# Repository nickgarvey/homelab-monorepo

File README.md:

# Nick's Homelab

Everything that runs the homelab, in one repo with one Nix flake:

* `hosts/`: NixOS configurations for each machine
* `modules/`: Reusable NixOS modules (e.g. `core/nixos-common` is applied to all hosts)
* `patches/`: Patches applied to upstream packages, and the ones worth upstreaming
* `secrets/`: SOPS-encrypted secrets for the hosts
* `docs/`: Notes and troubleshooting docs
* `devshells/`: Nix dev shells
* `packages/`: Software built here — packages, container images, and the `deploy` tool
* `k8s/`: Kubernetes manifests for the k3s cluster
* `firmware/`: ESP32 device firmware

Conventions for working in the repo are in [`AGENTS.md`](AGENTS.md).

## Hardware

| Host | Machine | CPU | RAM | GPU | Primary storage |
|------|---------|-----|-----|-----|-----------------|
| [`talos`](hosts/talos) | MSI PRO X870E-P WIFI | AMD Ryzen 9 9950X3D | 64 GB | NVIDIA RTX 5090 | Kingston SNV2S 500 GB NVMe + Crucial T705 4 TB NVMe |
| [`lydia`](hosts/lydia) | ASRock Industrial IMB-X1314 | Intel i5-12600K | 128 GB | iGPU (UHD 770) | Samsung 980 Pro 2 TB NVMe + 2× WDC 6 TB HDD |
| [`fus`](hosts/fus) | Beelink EQ14 Mini PC | Intel N150 | 16 GB | iGPU (Alder Lake-N) | Crucial P3 500 GB NVMe |
| [`ro`](hosts/ro) | Beelink EQ14 Mini PC | Intel N150 | 16 GB | iGPU (Alder Lake-N) | Crucial P3 500 GB NVMe |
| [`dah`](hosts/dah) | Beelink EQ14 Mini PC | Intel N150 | 16 GB | iGPU (Alder Lake-N) | Crucial P3 500 GB NVMe |
| [`joor`](hosts/joor) | Beelink EQi Mini PC | Intel Core 3 304 (Wildcat Lake) | 32 GB | iGPU (Xe, Wildcat Lake) | YMTC 512 GB UFS + WD Blue SN5100 4 TB NVMe |
| [`zah`](hosts/zah) | Beelink EQi Mini PC | Intel Core 3 304 (Wildcat Lake) | 32 GB | iGPU (Xe, Wildcat Lake) | YMTC 512 GB UFS + WD Blue SN5100 4 TB NVMe |
| [`frul`](hosts/frul) | Beelink EQi Mini PC | Intel Core 3 304 (Wildcat Lake) | 32 GB | iGPU (Xe, Wildcat Lake) | YMTC 512 GB UFS + WD Blue SN5100 4 TB NVMe |
| [`wabbajack`](hosts/wabbajack) | Framework Desktop | AMD Ryzen AI Max+ 395 (Strix Halo) | 128 GB | Radeon 8060S iGPU | WD_BLACK SN850X 2 TB NVMe + WD_BLACK SN7100 2 TB NVMe |
| [`dovahkiin`](hosts/dovahkiin) | Framework Laptop 13 | AMD Ryzen AI 7 350 | 64 GB | Radeon 860M iGPU | KIOXIA 2 TB NVMe |
| [`dragonsreach`](hosts/dragonsreach) | Topton Fanless PC| Intel N150 | 16 GB | iGPU (Alder Lake-N) | Samsung 870 QVO 1 TB SATA |
| [`skyforge`](hosts/skyforge) | Raspberry Pi 5 | Broadcom BCM2712 | — | VideoCore VII | microSD |

### Kubernetes Hosts

`fus`, `ro` and `dah` are the control-plane nodes of the Kubernetes cluster.
`joor`, `zah` and `frul` join as workers (`services.k3s.role = "agent"`) and also
run the Ceph storage cluster on their 4 TB drives.

[`modules/k3s/k3s-common.nix`](modules/k3s/k3s-common.nix) contain the main configuration for those hosts.

Services running on that cluster are found in [`k8s/`](k8s/).

### Servers

`lydia` has 128GB of DDR4 ECC RAM, so it acts as a storage/VM server.

`wabbajack` is the 128GB model of the Framework Desktop.

### Workstations
`talos` is the big desktop: 9950X3D and an RTX 5090, on a 500GB OS drive plus a 4TB btrfs carrying `/nix`, `/home` and `/var`.

`dovahkiin` is a AMD Ryzen AI 7 350 mainboard laptop with 64GB RAM I got off eBay. Eager to upgrade to a Panther Lake mainboard but going to wait for RAM to come down.

### Router
TopTon fanless PC with an Intel N150. 4x 2.5G NICs but I only use two of them (WAN/LAN).

## Installing a new host

Machines PXE-boot the live rescue/install environment off the LAN — `lydia`
serves it, no USB stick needed. See [`docs/netboot.md`](docs/netboot.md).

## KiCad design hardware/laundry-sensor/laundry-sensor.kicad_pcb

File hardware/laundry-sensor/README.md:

# laundry-sensor

Battery-powered vibration sensor for the washer: ESP32-C6 module, LIS2DW12
accelerometer, SHT40, 2×AA through a TPS63900 buck-boost, reporting over
Matter/Thread. Firmware lives in `firmware/devices/laundry-sensor/`.

Work in `nix develop .#pcb`.

- `circuit.py`: the circuit in SKiDL. `python3 circuit.py` runs ERC and writes `laundry-sensor.net`.
- `report.py`: prints the parts list and every net as Markdown, for review.
- `gen_footprints.py`: writes footprints KiCad's libraries lack (LIS2DW12) into `footprints/laundry.pretty`.
- `build_pcb.py`: writes `laundry-sensor.kicad_pcb` from the circuit: footprints, nets, placement, outline.
- `check.sh [dir]`: design-rule check summary plus top/bottom SVG renders.
- `route_pcb.py`: routes the board in place (run after `build_pcb.py`): net classes, the TPS63900
  loops by hand, a via from every SMD GND pad, Freerouting for the rest, then ground pours on both
  layers with stitching vias. Freerouting varies between runs, so it keeps the best of up to five.
- `fab.py`: writes JLCPCB files into `fab/`: `laundry-sensor-gerbers.zip`, `laundry-sensor-bom.csv`
  and `laundry-sensor-cpl.csv`. Its `CORRECTIONS` table turns KiCad rotations and origins into
  JLC's (EasyEDA's) for the packages that differ.

## Ordering from JLCPCB

1. Upload `fab/laundry-sensor-gerbers.zip`. 2 layers, 1.6 mm, 87×37 mm; defaults otherwise
   (lead-free HASL is fine; ENIG is flatter for the 0.5 mm-pitch LGA and WSON).
2. Turn on PCB Assembly, top side, Standard (JLC places the ESP32 module only with Standard).
   Edge rails added by JLC go on the long sides; snap them off after assembly. Upload the BOM and CPL.
3. In the placement preview, check pin 1 of U1 (TPS63900), U3 (LIS2DW12) and U4 (SHT40), and the
   outline of U2 (ESP32-C6 module). Their rotations and origins come from fitting the EasyEDA
   footprints to KiCad's, but JLC can keep its own per-part rotation.
4. BT1 (battery holder, back side) and J2 (PPK2 header) are through-hole and not in the BOM:
   solder them by hand. Fit a jumper on J2 unless a PPK2 is connected.

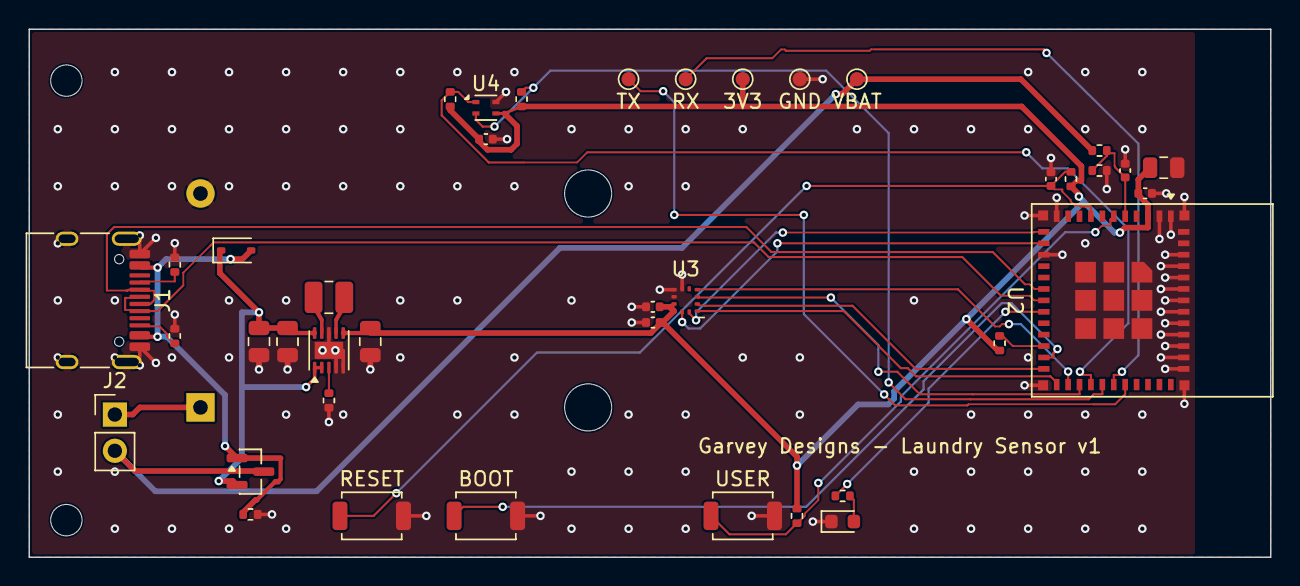
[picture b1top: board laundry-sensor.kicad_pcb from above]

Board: 2 copper layers, 87.0 x 37.0 mm, 43 parts (1 on the bottom side), 30 nets.

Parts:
BT1: 2xAA; BatteryHolder_Keystone_2462_2xAA
C1, C2, C3, C5: 22uF; C_0805_2012Metric
C4, C6, C7, C8, C9, C10: 100nF; C_0402_1005Metric
D1: 1N4148WS; D_SOD-323
D2: red; LED_0603_1608Metric
H1, H2: MountingHole_2.2mm_M2
J1: USB_C_Receptacle_USB2.0_16P; USB_C_Receptacle_HRO_TYPE-C-31-M-12
J2: PPK2; PinHeader_1x02_P2.54mm_Vertical
L1: 2.2uH; L_1008_2520Metric
Q1: AO3401A; SOT-23
R1, R5, R7: 100k; R_0402_1005Metric
R2: 36.5k; R_0402_1005Metric
R3, R4: 10M; R_0402_1005Metric
R6, R11, R12: 10k; R_0402_1005Metric
R8, R9, R10: 5.1k; R_0402_1005Metric
SW1: RESET; SW_SPST_TS-1088-xR020
SW2: BOOT; SW_SPST_TS-1088-xR020
SW3: USER; SW_SPST_TS-1088-xR020
TP1: TX; TestPoint_Pad_D1.0mm
TP2: RX; TestPoint_Pad_D1.0mm
TP3: 3V3; TestPoint_Pad_D1.0mm
TP4: GND; TestPoint_Pad_D1.0mm
TP5: VBAT; TestPoint_Pad_D1.0mm
U1: TPS63900; WSON-10-1EP_2.5x2.5mm_P0.5mm_EP1.2x2mm
U2: ESP32-C6-MINI-1
U3: LIS2DW12; LIS2DW12_LGA-12_2x2mm_P0.5mm
U4: SHT40-AD1B; Sensirion_DFN-4_1.5x1.5mm_P0.8mm_SHT4x_NoCentralPad

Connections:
+3V3: C3.1, C5.1, C6.1, C8.1, C9.1, C10.1, R5.1, R6.1, R7.1, R11.1, R12.1, TP3.1, U1.6, U2.3, U3.9, U3.10, U4.3
ACC_CS: U2.24, U3.2
ACC_INT1: U2.12, U3.12
ACC_INT2: U2.13, U3.11
ACC_MISO: U2.27, U3.3
ACC_MOSI: U2.26, U3.4
ACC_SCLK: U2.25, U3.1
BAT+: BT1.1, J2.1
BOOT: SW2.1, U2.23
EN: C7.1, R5.2, SW1.1, U2.8
GND: BT1.2, C1.2, C2.2, C3.2, C4.2, C5.2, C6.2, C7.2, C8.2, C9.2, C10.2, D2.1, J1.A1, J1.A12, J1.B1, J1.B12, J1.SH, R1.2, R2.2, R4.2, R9.2, R10.2, SW1.2, SW2.2, SW3.2, TP4.1, U1.4, U1.5, U1.8, U1.11, U2.1, U2.2, U2.11, U2.14, U2.36, U2.37, U2.38, U2.39, U2.40, U2.41, U2.42, U2.43, U2.44, U2.45, U2.46, U2.47, U2.48, U2.49, U2.50, U2.51, U2.52, U2.53, U3.6, U3.7, U3.8, U4.4
I2C_SCL: R12.2, U2.29, U4.2
I2C_SDA: R11.2, U2.28, U4.1
LED_A: D2.2, R8.2
unnamed: R2.1, U1.3
unnamed: L1.1, U1.9
unnamed: L1.2, U1.7
unnamed: R6.2, U2.22
unnamed: R8.1, U2.19
unnamed: J1.A5, R9.1
unnamed: J1.B5, R10.1
UART_RX: TP2.1, U2.30
UART_TX: TP1.1, U2.31
USB_D+: J1.A6, J1.B6, U2.18
USB_D-: J1.A7, J1.B7, U2.17
USER_BTN: R7.2, SW3.1, U2.6
VBAT: J2.2, Q1.3, R3.1, TP5.1
VBAT_SENSE: C4.1, R3.2, R4.1, U2.5
VBUS: D1.2, J1.A4, J1.A9, J1.B4, J1.B9, Q1.1, R1.1
VIN: C1.1, C2.1, D1.1, Q1.2, U1.1, U1.2, U1.10

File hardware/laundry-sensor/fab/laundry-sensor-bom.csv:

Comment,Designator,Footprint,LCSC Part #
22uF,"C1,C2,C3,C5",C_0805_2012Metric,C45783
100nF,"C4,C6,C7,C8,C9,C10",C_0402_1005Metric,C1525
1N4148WS,D1,D_SOD-323,C2128
red,D2,LED_0603_1608Metric,C2286
USB_C_Receptacle_USB2.0_16P,J1,USB_C_Receptacle_HRO_TYPE-C-31-M-12,C165948
2.2uH,L1,L_1008_2520Metric,C1017131
AO3401A,Q1,SOT-23,C15127
100k,"R1,R5,R7",R_0402_1005Metric,C25741
36.5k,R2,R_0402_1005Metric,C25887
10M,"R3,R4",R_0402_1005Metric,C144806
10k,"R6,R11,R12",R_0402_1005Metric,C25744
5.1k,"R8,R9,R10",R_0402_1005Metric,C25905
RESET,SW1,SW_SPST_TS-1088-xR020,C720477
BOOT,SW2,SW_SPST_TS-1088-xR020,C720477
USER,SW3,SW_SPST_TS-1088-xR020,C720477
TPS63900,U1,WSON-10-1EP_2.5x2.5mm_P0.5mm_EP1.2x2mm,C1518762
ESP32-C6-MINI-1,U2,ESP32-C6-MINI-1,C5736265
LIS2DW12,U3,LIS2DW12_LGA-12_2x2mm_P0.5mm,C189624
SHT40-AD1B,U4,Sensirion_DFN-4_1.5x1.5mm_P0.8mm_SHT4x_NoCentralPad,C2909890

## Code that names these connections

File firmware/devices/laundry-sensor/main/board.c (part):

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/* hardware/laundry-sensor/circuit.py */
#define PIN_LED        GPIO_NUM_14   /* through 5.1k to the LED, active high */
#define PIN_BUTTON     GPIO_NUM_3    /* USER, 100k pull-up on the board, active low */
#define PIN_ACC_INT1   GPIO_NUM_0
#define PIN_ACC_INT2   GPIO_NUM_1
#define PIN_ACC_CS     GPIO_NUM_18
#define PIN_ACC_SCLK   GPIO_NUM_19
#define PIN_ACC_MOSI   GPIO_NUM_20
#define PIN_ACC_MISO   GPIO_NUM_21
#define PIN_I2C_SDA    GPIO_NUM_22
#define PIN_I2C_SCL    GPIO_NUM_23
#define PIN_VBAT_SENSE GPIO_NUM_2
#else
/* Adafruit ESP32-C6 Feather */
#define PIN_LED        GPIO_NUM_15   /* red LED, active high */
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static bool accel_init(void)
{
    spi_bus_config_t bus = {
        .mosi_io_num = PIN_ACC_MOSI,
        .miso_io_num = PIN_ACC_MISO,
        .sclk_io_num = PIN_ACC_SCLK,
        .quadwp_io_num = -1,
        .quadhd_io_num = -1,
    };
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        .address_bits = 8,
        .mode = 3,                     /* CPOL = 1, CPHA = 1 (DS11811 section 6.2) */
        .clock_speed_hz = 1000000,
        .spics_io_num = PIN_ACC_CS,
        .queue_size = 1,
    };
    if (spi_bus_initialize(SPI2_HOST, &bus, SPI_DMA_DISABLED) != ESP_OK ||
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        ESP_LOGE(TAG, "LIS2DW12 not found");
        return false;
    }
    irq_setup(&s_wake_irq, PIN_ACC_INT1, BOARD_NOTIFY_ACCEL_WAKE, true, false);
    irq_setup(&s_fifo_irq, PIN_ACC_INT2, BOARD_NOTIFY_ACCEL_FIFO, true, false);
    return true;
}

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        out[i].y_mg = raw[i].y_mg;
        out[i].z_mg = raw[i].z_mg;
    }
    gpio_intr_enable(PIN_ACC_INT2);
    return n;
}

void board_accel_ack_wake(void)
{
    lis2dw12_clear_interrupts();
    gpio_intr_enable(PIN_ACC_INT1);
}

void board_fake_wash(bool on) { (void)on; }
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{
    i2c_master_bus_config_t bus_cfg = {
        .i2c_port = -1,
        .sda_io_num = PIN_I2C_SDA,
        .scl_io_num = PIN_I2C_SCL,
        .clk_source = I2C_CLK_SRC_DEFAULT,
        .glitch_ignore_cnt = 7,
        .flags.enable_internal_pullup = false,   /* 10k on the board */
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static bool battery_init(void)
{
    adc_unit_t unit;
    if (adc_oneshot_io_to_channel(PIN_VBAT_SENSE, &unit, &s_adc_chan) != ESP_OK) return false;
    adc_oneshot_unit_init_cfg_t unit_cfg = { .unit_id = unit };
    adc_oneshot_chan_cfg_t chan_cfg = { .atten = ADC_ATTEN_DB_12, .bitwidth = ADC_BITWIDTH_DEFAULT };
    adc_cali_curve_fitting_config_t cali_cfg = {
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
